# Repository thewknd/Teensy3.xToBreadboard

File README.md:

## Teensy 3.0 To Breadboard Adapter

## Features
- All Teensy 3.0 pins accessible 
- RTC battery
- Reset button
- TWI Pullup

## Download
- V3: ---
- V2: no download link
- V1: https://github.com/thewknd/Teensy3.0ToBreadboard/archive/V001.zip

## History

### V3
- RTC battery
- Reset button
- TWI Pullup

### V1
- All Teensy 3.0 pins accessible 

## License
Except where otherwise noted, this work is licensed under 

http://creativecommons.org/licenses/by-sa/3.0/

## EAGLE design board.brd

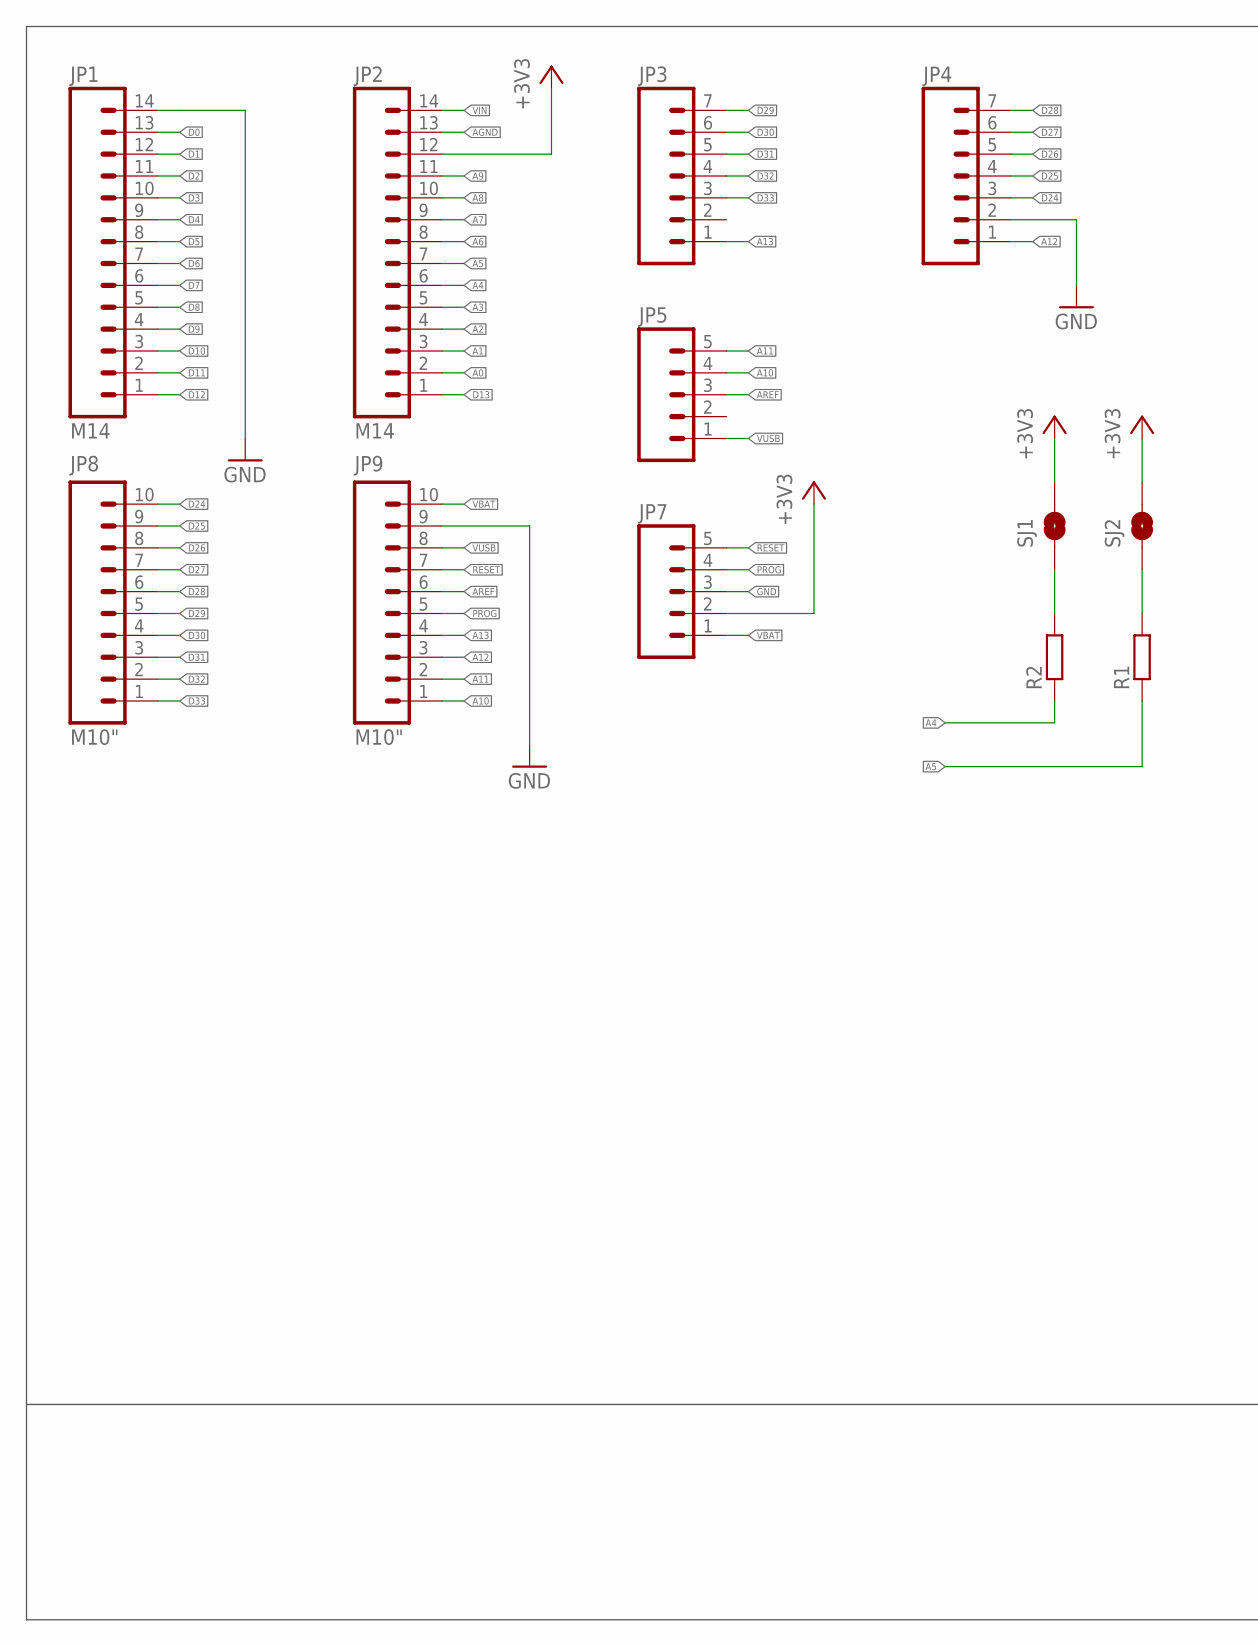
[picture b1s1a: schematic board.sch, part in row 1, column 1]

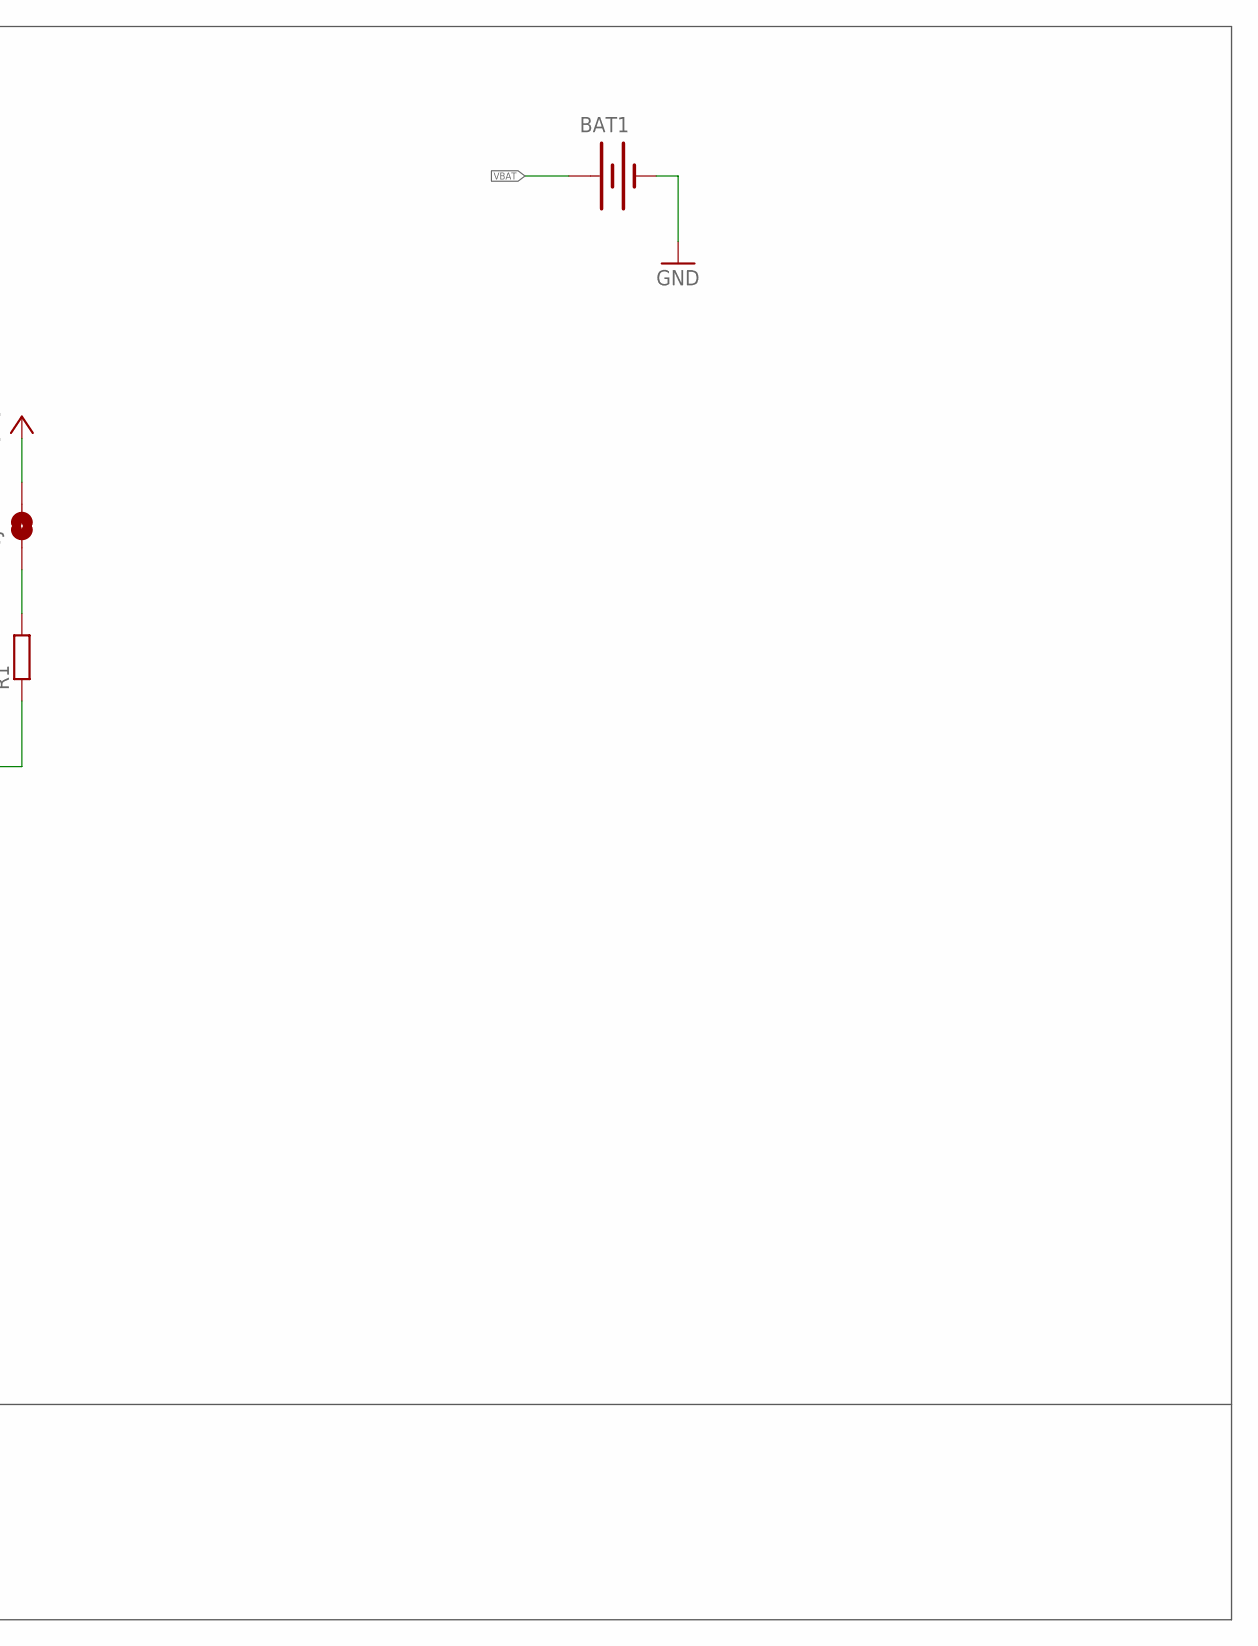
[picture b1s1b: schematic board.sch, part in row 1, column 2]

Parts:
BAT1: BATTERY12MM; BATTCON_12MM
JP1, JP2: M14; 1X14
JP3, JP4: M07; 1X07
JP5, JP7: M05PTH; 1X05
JP8, JP9: M10"; 1X10
R1, R2: RESISTOR; R0805
SJ1, SJ2: SOLDERJUMPERNO; SJ_2S-NO

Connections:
+3V3: JP2.12, JP7.2, SJ1.2, SJ2.2
A0: JP2.2
A1: JP2.3
A2: JP2.4
A3: JP2.5
A4: JP2.6, R2.1
A5: JP2.7, R1.1
A6: JP2.8
A7: JP2.9
A8: JP2.10
A9: JP2.11
A10: JP5.4, JP9.1
A11: JP5.5, JP9.2
A12: JP4.1, JP9.3
A13: JP3.1, JP9.4
AGND: JP2.13
AREF: JP5.3, JP9.6
D0: JP1.13
D1: JP1.12
D2: JP1.11
D3: JP1.10
D4: JP1.9
D5: JP1.8
D6: JP1.7
D7: JP1.6
D8: JP1.5
D9: JP1.4
D10: JP1.3
D11: JP1.2
D12: JP1.1
D13: JP2.1
D24: JP4.3, JP8.10
D25: JP4.4, JP8.9
D26: JP4.5, JP8.8
D27: JP4.6, JP8.7
D28: JP4.7, JP8.6
D29: JP3.7, JP8.5
D30: JP3.6, JP8.4
D31: JP3.5, JP8.3
D32: JP3.4, JP8.2
D33: JP3.3, JP8.1
GND: BAT1.GND (-), JP1.14, JP4.2, JP7.3, JP9.9
unnamed: R2.2, SJ1.1
unnamed: R1.2, SJ2.1
PROG: JP7.4, JP9.5
RESET: JP7.5, JP9.7
VBAT: BAT1.PWR@1 (+), JP7.1, JP9.10
VIN: JP2.14
VUSB: JP5.1, JP9.8

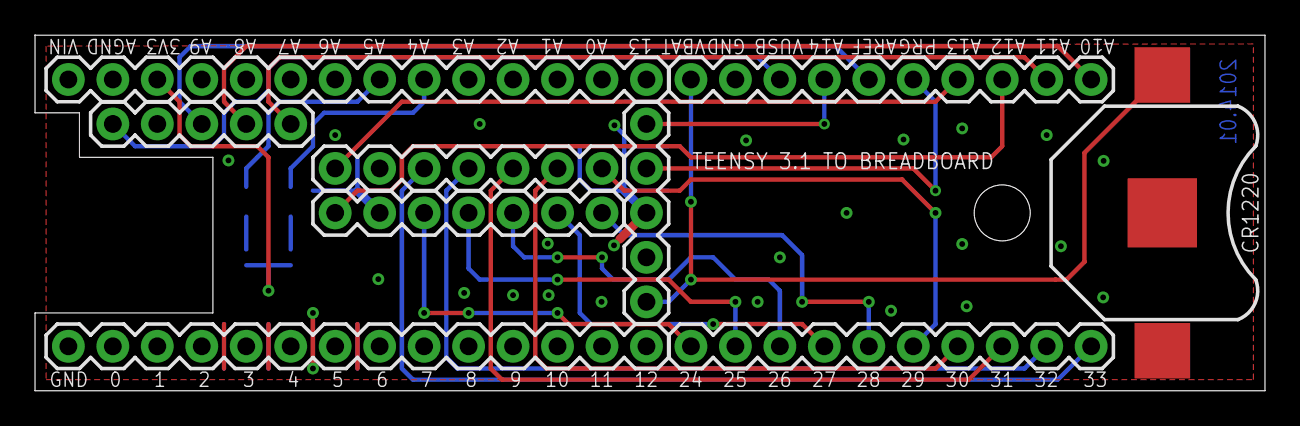
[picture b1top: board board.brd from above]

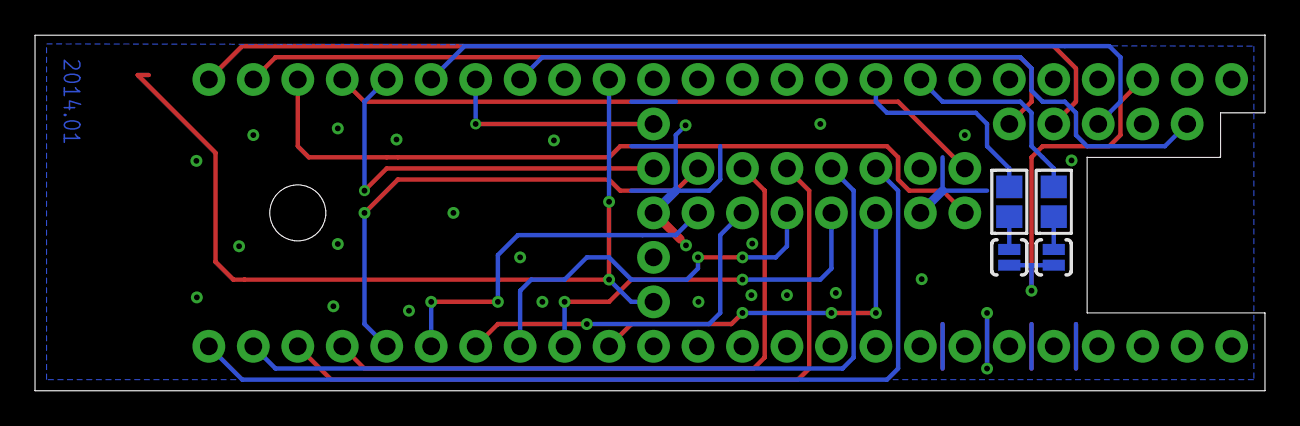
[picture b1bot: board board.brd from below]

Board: 2 copper layers, 70.3 x 20.3 mm, 13 parts (4 on the bottom side), 25 nets.

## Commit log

2013-01-16 inital V3 commit
2013-01-22 new reset button
2014-04-02 new readme file
2014-04-02 rename README to README.mk
2014-04-02 Revert "rename README to README.mk"
    This reverts commit b80500548cdd2cd70c6c509ec3b8d60bb767451d.
2014-04-02 rename README to README.md

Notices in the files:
parts and their libraries:
SparkFun-Connectors: Licensing: CC v3.0 Share-Alike You are welcome to use this library for commercial purposes.
